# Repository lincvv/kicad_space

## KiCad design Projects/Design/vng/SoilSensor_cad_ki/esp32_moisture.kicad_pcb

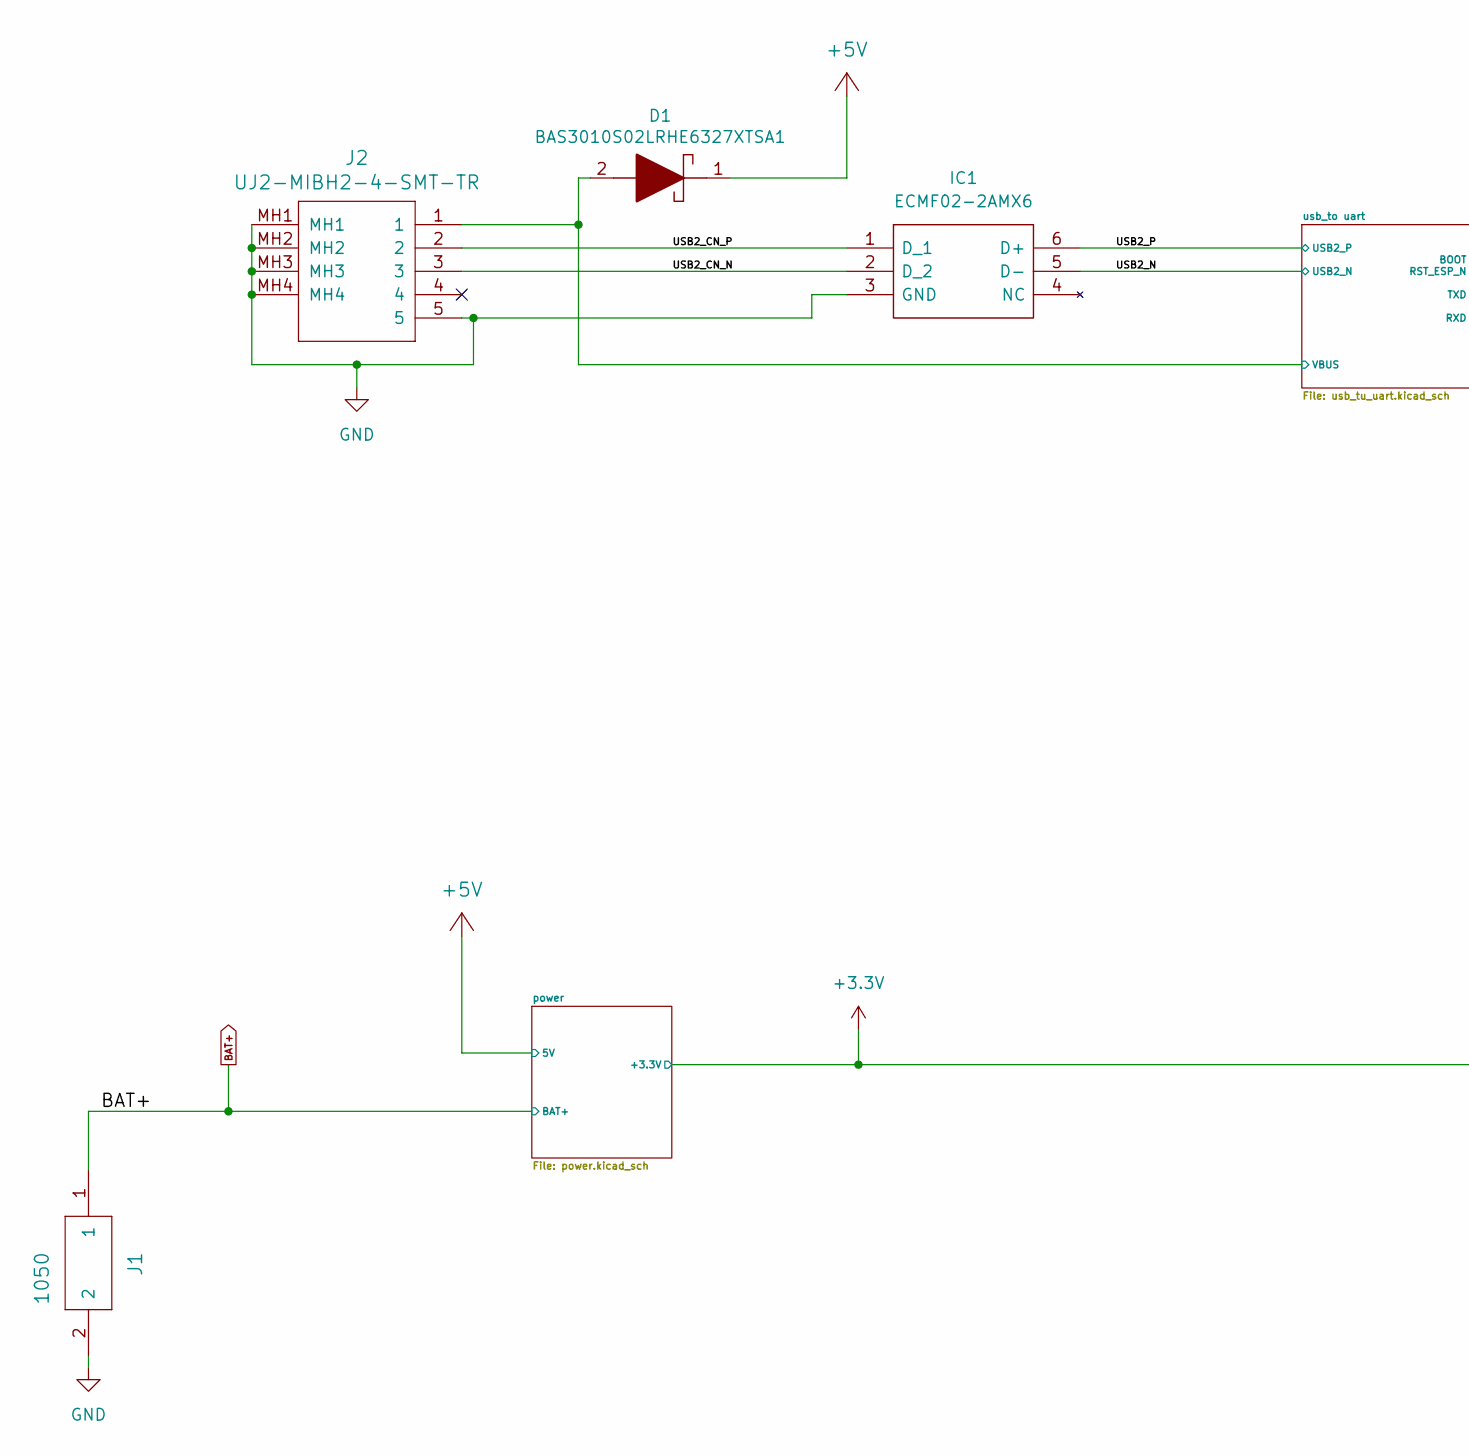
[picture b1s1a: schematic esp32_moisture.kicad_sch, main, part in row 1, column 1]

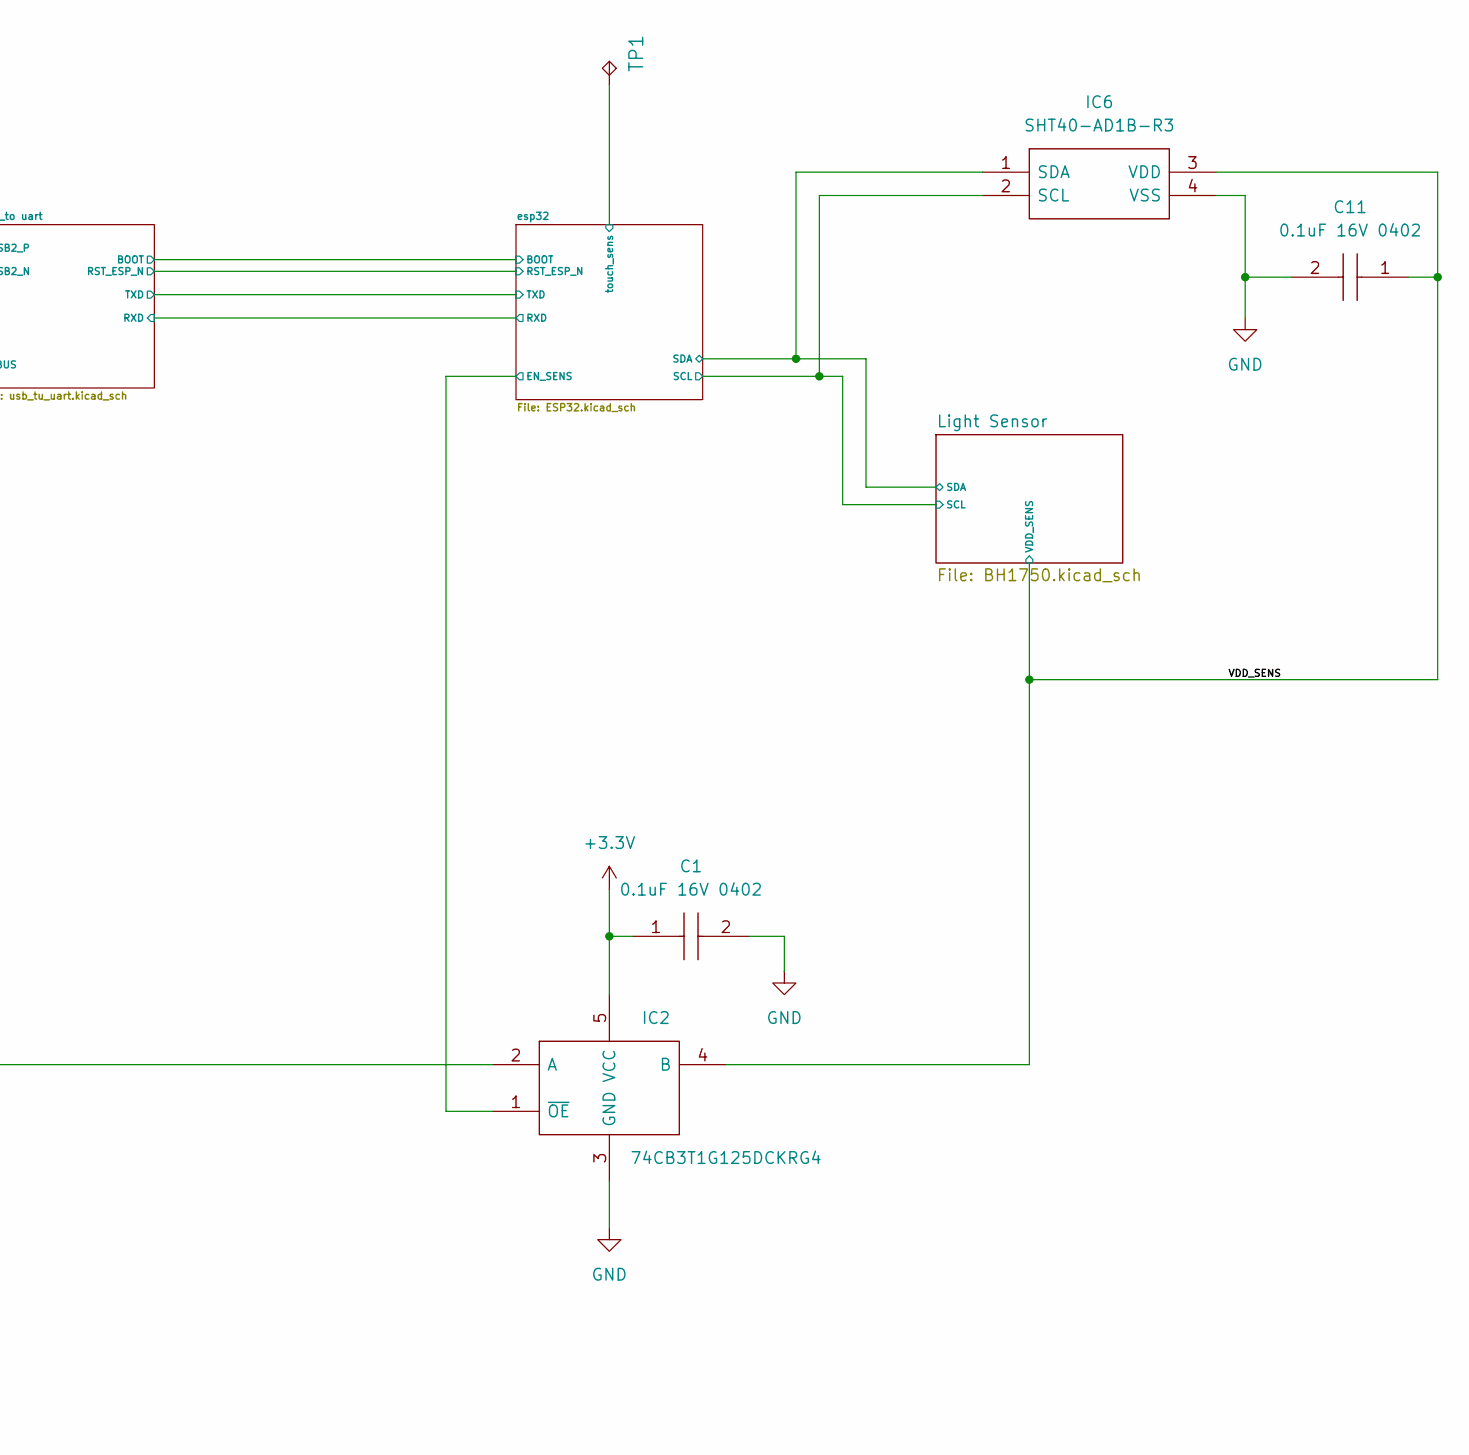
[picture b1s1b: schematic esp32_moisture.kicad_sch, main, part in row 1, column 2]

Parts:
C1, C11: 0.1uF 16V 0402; C_0402_1005Metric; Manufacturer_Part_Number GRM155R71C104KA88D; Mouser Part Number N/A
D1: BAS3010S02LRHE6327XTSA1; Manufacturer_Part_Number BAS3010S02LRHE6327XTSA1; Mouser Part Number 726-3010S02LRHXTSA1
IC1: ECMF02-2AMX6; SON50P150X170X55-6N-D; Manufacturer_Part_Number ECMF02-2AMX6; Mouser Part Number 511-ECMF02-2AMX6
IC2: 74CB3T1G125DCKRG4; SOT65P210X110-5N; Manufacturer_Part_Number 74CB3T1G125DCKRG4; Mouser Part Number 595-CB3T1G125DCKRG4
IC6: SHT40-AD1B-R3; SHT40AD1BR3; Manufacturer_Part_Number SHT40-AD1B-R3; Mouser Part Number 403-SHT40-AD1B-R3
J1: 1050
J2: UJ2-MIBH2-4-SMT-TR; UJ2MIBH24SMTTR
TP1: TPTP15R; TP15R

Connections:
+3.3V: C1.1, IC2.2 (A), IC2.5 (VCC); also elsewhere on the board
+5V: D1.1; also elsewhere on the board
/USB2_CN_N: IC1.2 (D_2), J2.3
/USB2_CN_P: IC1.1 (D_1), J2.2
/USB2_N: IC1.5 (D-); also elsewhere on the board
/USB2_P: IC1.6 (D+); also elsewhere on the board
/VDD_SENS: C11.1, IC2.4 (B), IC6.3 (VDD); also elsewhere on the board
/esp32/EN_SENS: IC2.1 (~OE); also elsewhere on the board
/esp32/SCL: IC6.2 (SCL); also elsewhere on the board
/esp32/SDA: IC6.1 (SDA); also elsewhere on the board
/esp32/touch_sens: TP1.TP; also elsewhere on the board
/usb_to uart/VBUS: D1.2, J2.1; also elsewhere on the board
BAT+: J1.1; also elsewhere on the board
GND: C1.2, C11.2, IC1.3 (GND), IC2.3 (GND), IC6.4 (VSS), J1.2, J2.5, J2.MH1, J2.MH2, J2.MH3, J2.MH4; also elsewhere on the board

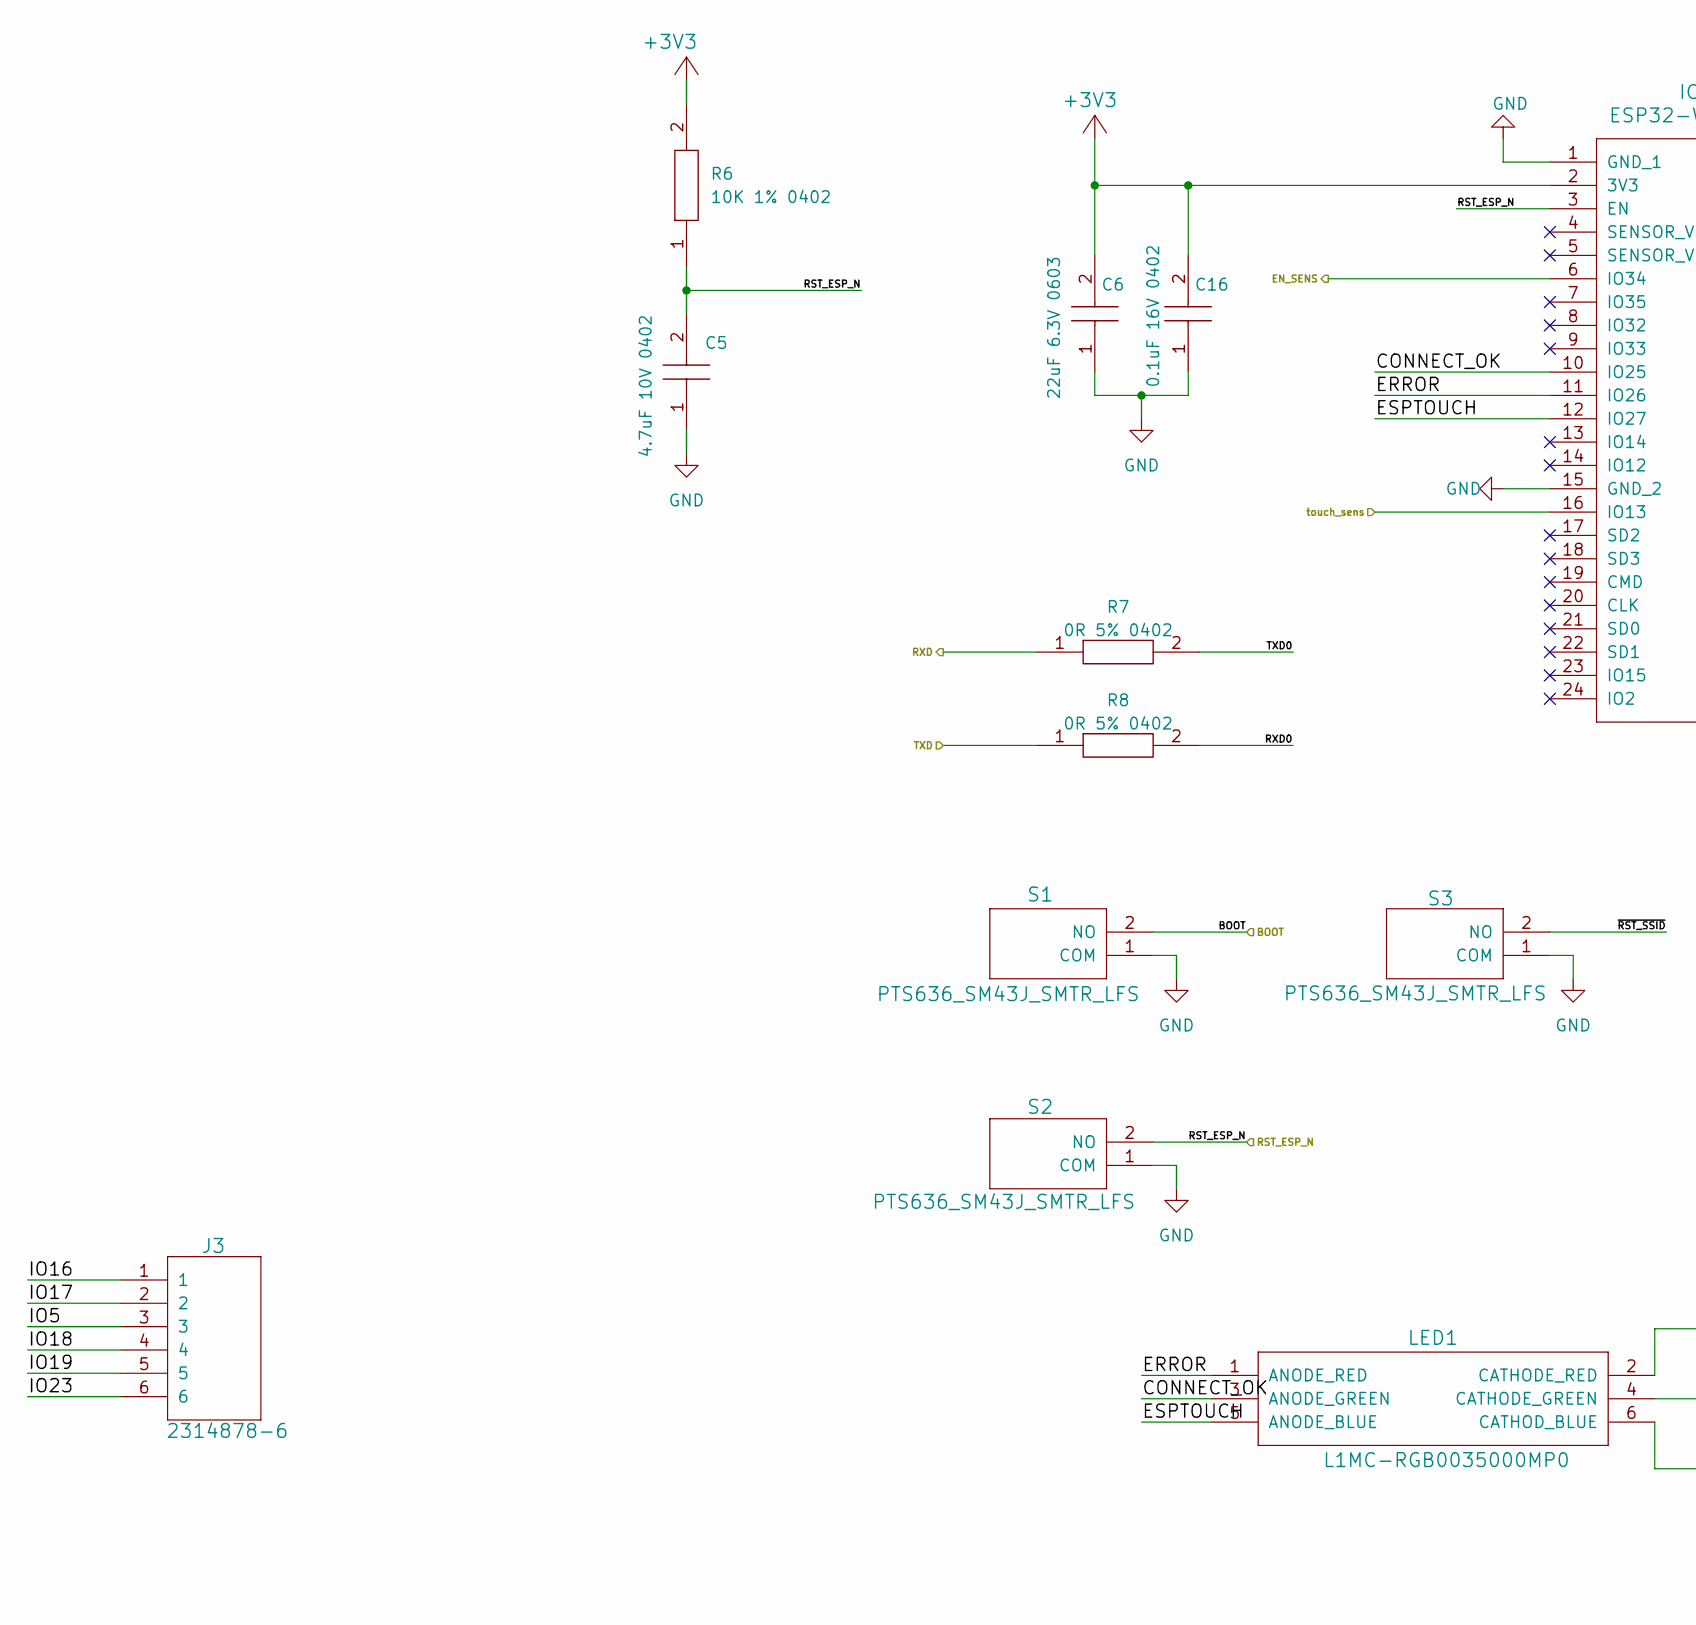
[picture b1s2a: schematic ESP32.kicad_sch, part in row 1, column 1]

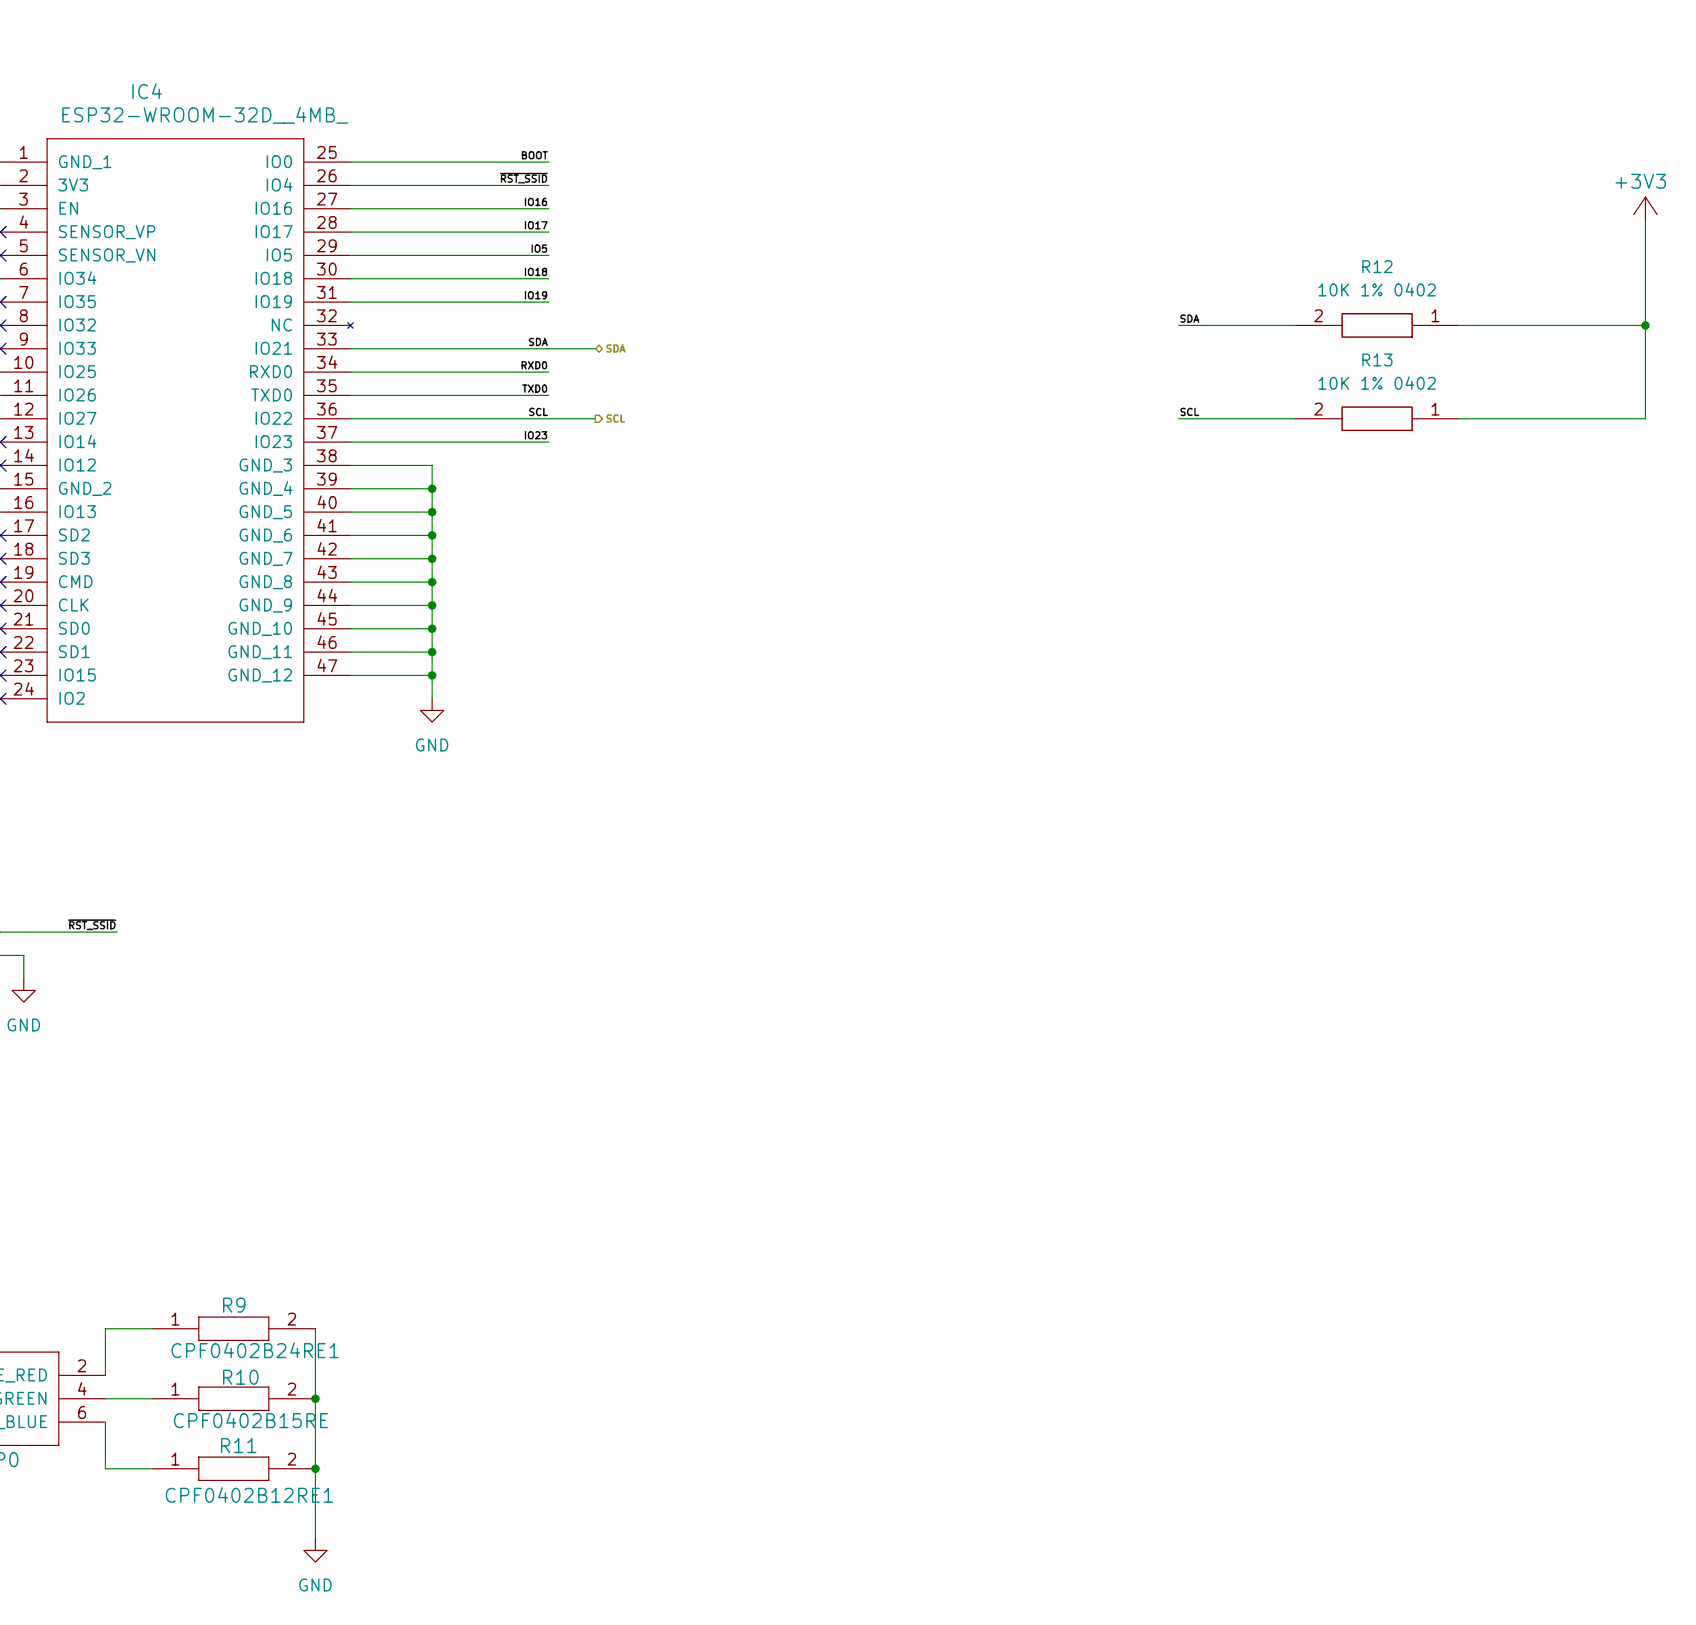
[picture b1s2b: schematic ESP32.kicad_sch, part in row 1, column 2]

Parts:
C5: 4.7uF 10V 0402; C_0402_1005Metric; Manufacturer_Part_Number C1005X5R1A475K050BC; Mouser Part Number 810-C1005X5R1A475KBC
C6: 22uF 6.3V 0603; C_0603_1608Metric; Manufacturer_Part_Number GRM188R60J226MEA0D; Mouser Part Number 81-GRM188R60J226ME0D
C16: 0.1uF 16V 0402; C_0402_1005Metric; Manufacturer_Part_Number GRM155R71C104KA88D; Mouser Part Number N/A
IC4: ESP32-WROOM-32D__4MB_; ESP32WROOM32D4MB
J3: 2314878-6; RHDR6W40P0X200_1X6_1200X210X45
LED1: L1MC-RGB0035000MP0; L1MCRGB0035000MP0
R6, R12, R13: 10K 1% 0402; R_0402_1005Metric; Manufacturer_Part_Number AC0402FR-0710KL; Mouser Part Number 603-AC0402FR-0710KL
R7, R8: 0R 5% 0402; R_0402_1005Metric; Manufacturer_Part_Number CR0402-J/-000GLF; Mouser Part Number 652-CR0402-J/-000GLF
R9: CPF0402B24RE1; RESC1005X35N
R10: CPF0402B15RE; RESC1005X35N
R11: CPF0402B12RE1; RESC1005X35N
S1, S2, S3: PTS636_SM43J_SMTR_LFS; PTS636SM43JSMTRLFS

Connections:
+3V3: C6.2, C16.2, IC4.2 (3V3), R6.2, R12.1, R13.1
/esp32/BOOT: IC4.25 (IO0), S1.2 (NO); also elsewhere on the board
/esp32/CONNECT_OK: IC4.10 (IO25), LED1.3 (ANODE_GREEN)
/esp32/EN_SENS: IC4.6 (IO34); also elsewhere on the board
/esp32/ERROR: IC4.11 (IO26), LED1.1 (ANODE_RED)
/esp32/ESPTOUCH: IC4.12 (IO27), LED1.5 (ANODE_BLUE)
/esp32/IO5: IC4.29 (IO5), J3.3
/esp32/IO16: IC4.27 (IO16), J3.1
/esp32/IO17: IC4.28 (IO17), J3.2
/esp32/IO18: IC4.30 (IO18), J3.4
/esp32/IO19: IC4.31 (IO19), J3.5
/esp32/IO23: IC4.37 (IO23), J3.6
/esp32/RST_ESP_N: C5.2, IC4.3 (EN), R6.1, S2.2 (NO); also elsewhere on the board
/esp32/RXD: R7.1; also elsewhere on the board
/esp32/RXD0: IC4.34 (RXD0), R8.2
/esp32/SCL: IC4.36 (IO22), R13.2; also elsewhere on the board
/esp32/SDA: IC4.33 (IO21), R12.2; also elsewhere on the board
/esp32/TXD: R8.1; also elsewhere on the board
/esp32/TXD0: IC4.35 (TXD0), R7.2
/esp32/touch_sens: IC4.16 (IO13); also elsewhere on the board
/esp32/~RST_SSID: IC4.26 (IO4), S3.2 (NO)
GND: C5.1, C6.1, C16.1, IC4.1 (GND_1), IC4.15 (GND_2), IC4.38 (GND_3), IC4.39 (GND_4), IC4.40 (GND_5), IC4.41 (GND_6), IC4.42 (GND_7), IC4.43 (GND_8), IC4.44 (GND_9), IC4.45 (GND_10), IC4.46 (GND_11), IC4.47 (GND_12), R9.2, R10.2, R11.2, S1.1 (COM), S2.1 (COM), S3.1 (COM); also elsewhere on the board
unnamed: LED1.2 (CATHODE_RED), R9.1
unnamed: LED1.4 (CATHODE_GREEN), R10.1
unnamed: LED1.6 (CATHOD_BLUE), R11.1

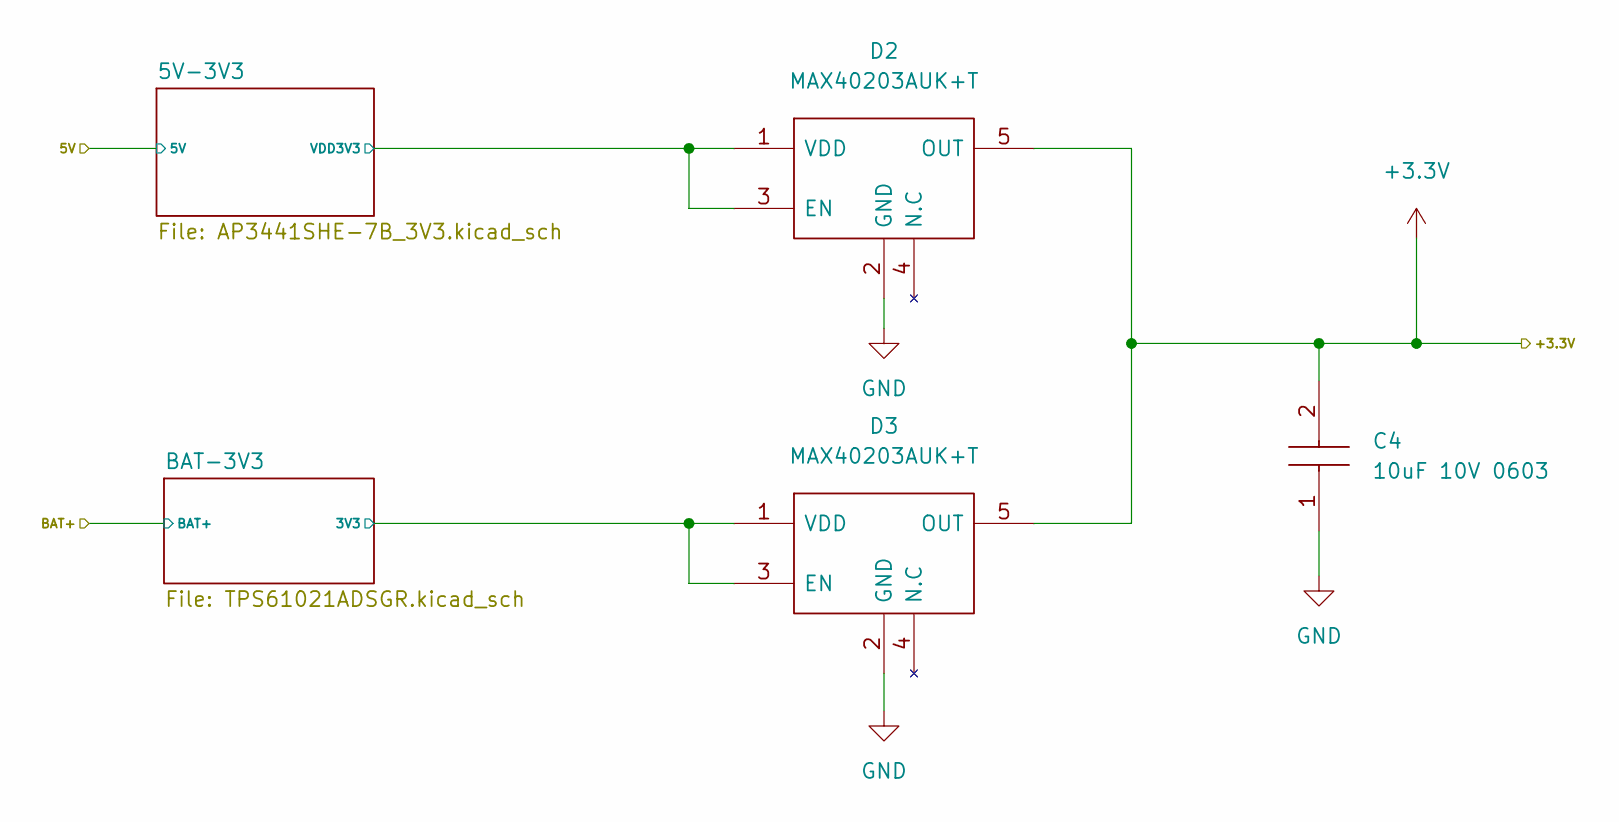
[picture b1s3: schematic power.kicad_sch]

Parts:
C4: 10uF 10V 0603; C_0603_1608Metric; Manufacturer_Part_Number GRM188Z71A106KA73D; Mouser Part Number 81-GRM188Z71A106KA3D
D2, D3: MAX40203AUK+T; SOT95P280X145-5N; Manufacturer_Part_Number MAX40203AUK+T; Mouser Part Number 700-MAX40203AUK+T

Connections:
+3.3V: C4.2, D2.5 (OUT), D3.5 (OUT); also elsewhere on the board
/power/5V-3V3/VDD3V3: D2.1 (VDD), D2.3 (EN); also elsewhere on the board
/power/BAT-3V3/VOUT_3V3: D3.1 (VDD), D3.3 (EN); also elsewhere on the board
GND: C4.1, D2.2 (GND), D3.2 (GND); also elsewhere on the board

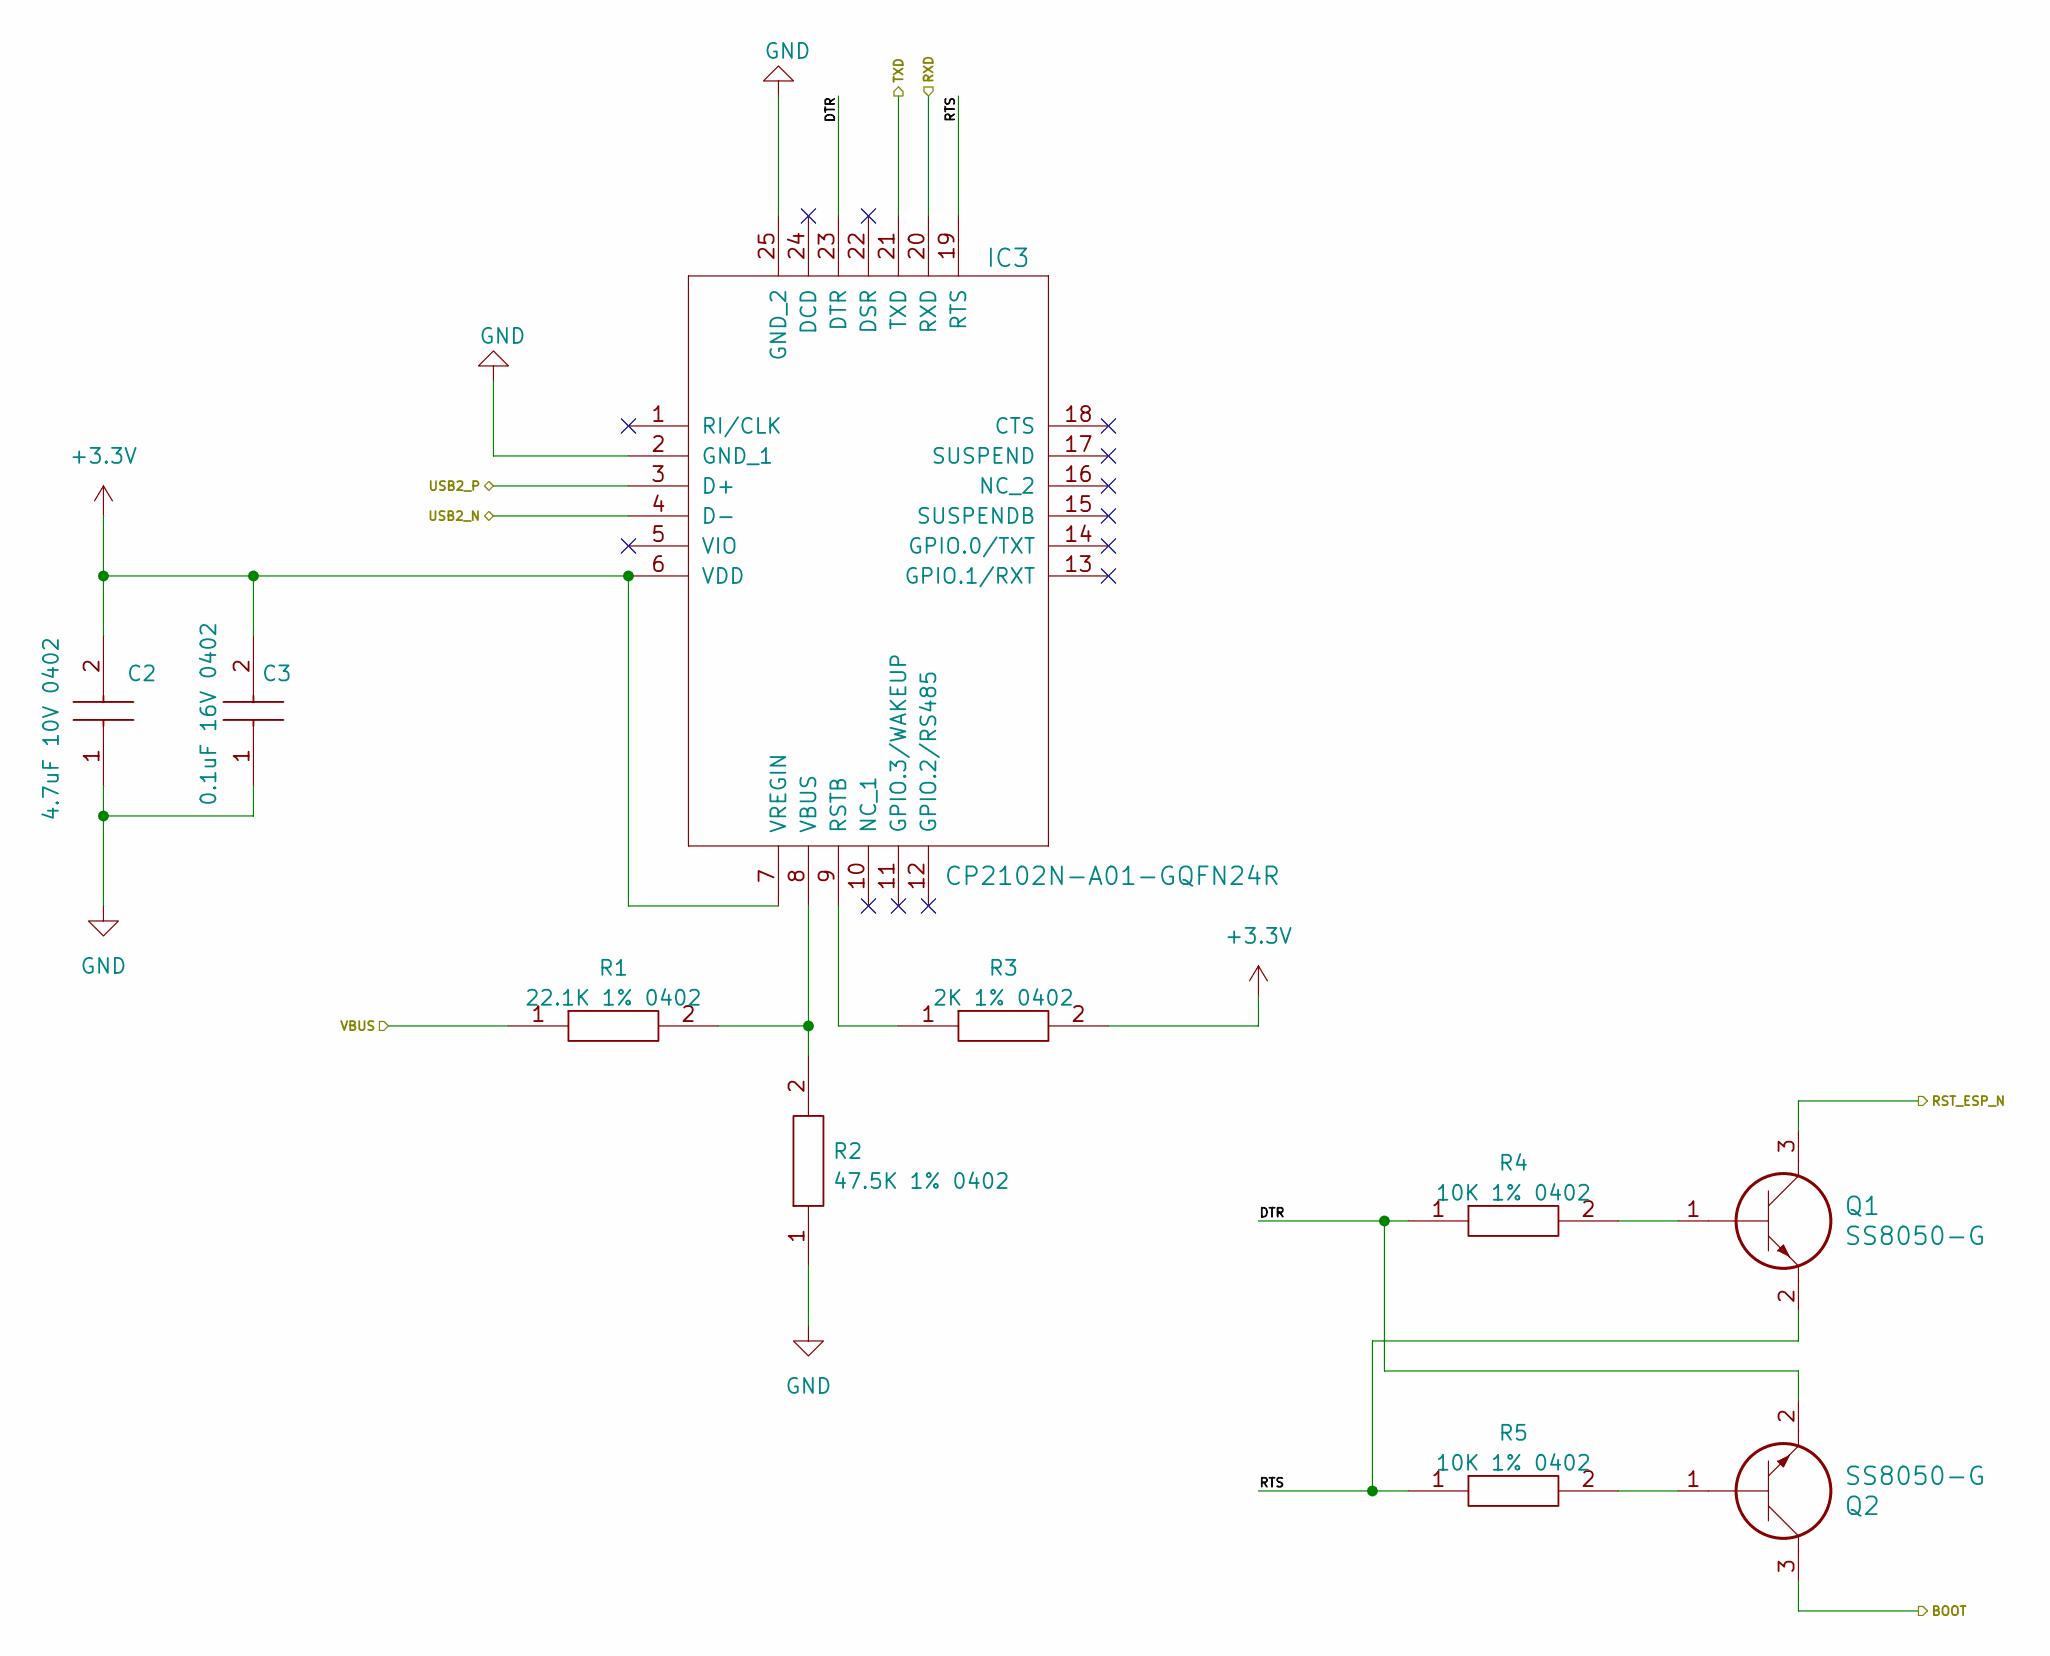
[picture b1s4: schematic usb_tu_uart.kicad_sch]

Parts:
C2: 4.7uF 10V 0402; C_0402_1005Metric; Manufacturer_Part_Number C1005X5R1A475K050BC; Mouser Part Number 810-C1005X5R1A475KBC
C3: 0.1uF 16V 0402; C_0402_1005Metric; Manufacturer_Part_Number GRM155R71C104KA88D; Mouser Part Number N/A
IC3: CP2102N-A01-GQFN24R; QFN50P400X400X80-25N
Q1, Q2: SS8050-G; SOT95P240X115-3N
R1: 22.1K 1% 0402; R_0402_1005Metric; Manufacturer_Part_Number CRCW040222K1FKED; Mouser Part Number 71-CRCW0402-22.1K-E3
R2: 47.5K 1% 0402; R_0402_1005Metric; Manufacturer_Part_Number RC0402FR-0747K5L; Mouser Part Number 603-RC0402FR-0747K5L
R3: 2K 1% 0402; R_0402_1005Metric; Manufacturer_Part_Number CR0402-FX-2001GLF; Mouser Part Number 652-CR0402FX-2001GLF
R4, R5: 10K 1% 0402; R_0402_1005Metric; Manufacturer_Part_Number AC0402FR-0710KL; Mouser Part Number 603-AC0402FR-0710KL

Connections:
+3.3V: C2.2, C3.2, IC3.6 (VDD), IC3.7 (VREGIN), R3.2; also elsewhere on the board
/USB2_N: IC3.4 (D-); also elsewhere on the board
/USB2_P: IC3.3 (D+); also elsewhere on the board
/esp32/BOOT: Q2.3 (C); also elsewhere on the board
/esp32/RST_ESP_N: Q1.3 (C); also elsewhere on the board
/esp32/RXD: IC3.20 (RXD); also elsewhere on the board
/esp32/TXD: IC3.21 (TXD); also elsewhere on the board
/usb_to uart/DTR: IC3.23 (DTR), Q2.2 (E), R4.1
/usb_to uart/RTS: IC3.19 (RTS), Q1.2 (E), R5.1
/usb_to uart/VBUS: R1.1; also elsewhere on the board
GND: C2.1, C3.1, IC3.2 (GND_1), IC3.25 (GND_2), R2.1; also elsewhere on the board
unnamed: IC3.8 (VBUS), R1.2, R2.2
unnamed: IC3.9 (RSTB), R3.1
unnamed: Q1.1 (B), R4.2
unnamed: Q2.1 (B), R5.2

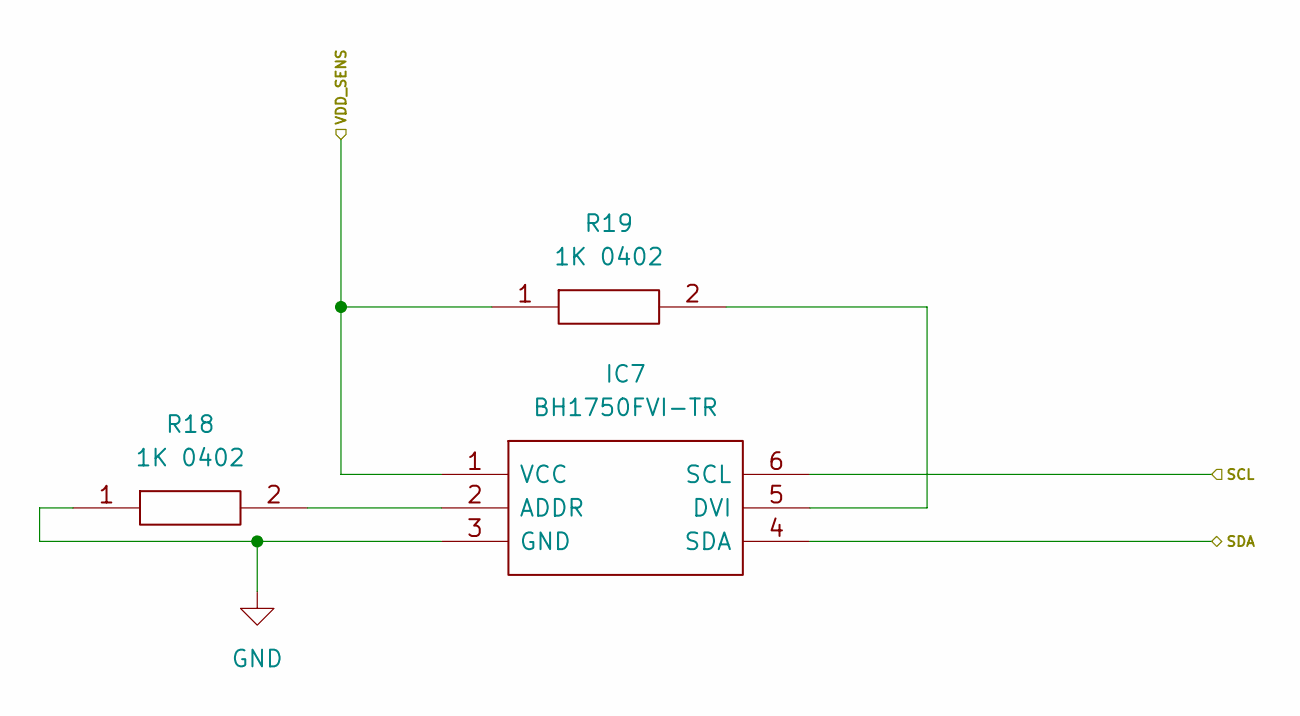
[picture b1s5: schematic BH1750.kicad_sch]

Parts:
IC7: BH1750FVI-TR; WSOF6; Manufacturer_Part_Number BH1750FVI-TR; Mouser Part Number 755-BH1750FVI-TR
R18, R19: 1K 0402; R_0402_1005Metric; Manufacturer_Part_Number RT0402FRE071KL; Mouser Part Number 603-RT0402FRE071KL

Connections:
/VDD_SENS: IC7.1 (VCC), R19.1; also elsewhere on the board
/esp32/SCL: IC7.6 (SCL); also elsewhere on the board
/esp32/SDA: IC7.4 (SDA); also elsewhere on the board
GND: IC7.3 (GND), R18.1; also elsewhere on the board
unnamed: IC7.2 (ADDR), R18.2
unnamed: IC7.5 (DVI), R19.2

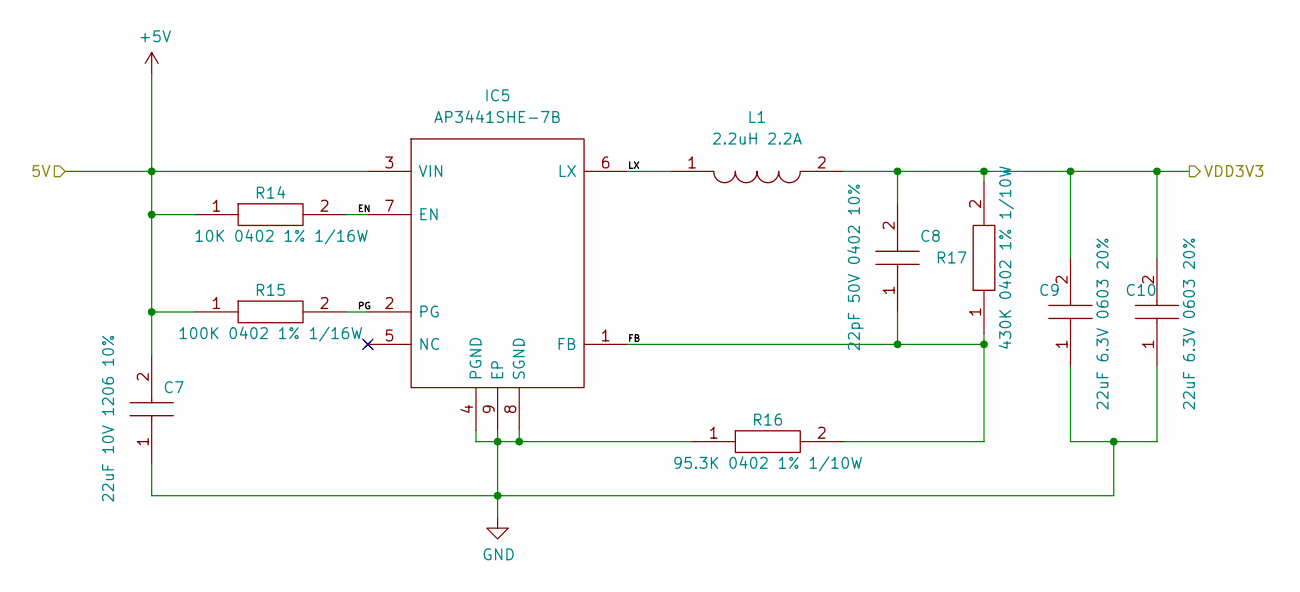
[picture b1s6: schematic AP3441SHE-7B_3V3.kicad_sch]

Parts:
C7: 22uF 10V 1206 10%; C_1206_3216Metric; Manufacturer_Part_Number GRM31CR71A226KE15L; Mouser Part Number 81-GRM31CR71A226K15L
C8: 22pF 50V 0402 10%; C_0402_1005Metric; Manufacturer_Part_Number C0402C220K5RACTU; Mouser Part Number 80-C0402C220K5RACTU
C9, C10: 22uF 6.3V 0603 20%; C_0603_1608Metric; Manufacturer_Part_Number GRM188R60J226MEA0D; Mouser Part Number 81-GRM188R60J226ME0D
IC5: AP3441SHE-7B; SON50P201X201X60-9N-D; Manufacturer_Part_Number AP3441SHE-7B; Mouser Part Number 621-AP3441SHE-7B
L1: 2.2uH 2.2A; DFE2HCAH1R0MJ0L; Manufacturer_Part_Number 1239AS-H-2R2M=P2; Mouser Part Number 81-1239AS-H-2R2MP2
R14: 10K 0402 1% 1/16W; R_0402_1005Metric; Manufacturer_Part_Number AC0402FR-0710KL; Mouser Part Number 603-AC0402FR-0710KL
R15: 100K 0402 1% 1/16W; R_0402_1005Metric; Manufacturer_Part_Number SFR01MZPF1003; Mouser Part Number 755-SFR01MZPF1003
R16: 95.3K 0402 1% 1/10W; R_0402_1005Metric; Manufacturer_Part_Number ERJ-U02F9532X; Mouser Part Number 667-ERJ-U02F9532X
R17: 430K 0402 1% 1/10W; R_0402_1005Metric; Manufacturer_Part_Number ERJ-U02F4303X

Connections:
+5V: C7.2, IC5.3 (VIN), R14.1, R15.1; also elsewhere on the board
/power/5V-3V3/EN: IC5.7 (EN), R14.2
/power/5V-3V3/FB: C8.1, IC5.1 (FB), R16.2, R17.1
/power/5V-3V3/LX: IC5.6 (LX), L1.1
/power/5V-3V3/PG: IC5.2 (PG), R15.2
/power/5V-3V3/VDD3V3: C8.2, C9.2, C10.2, L1.2, R17.2; also elsewhere on the board
GND: C7.1, C9.1, C10.1, IC5.4 (PGND), IC5.8 (SGND), IC5.9 (EP), R16.1; also elsewhere on the board

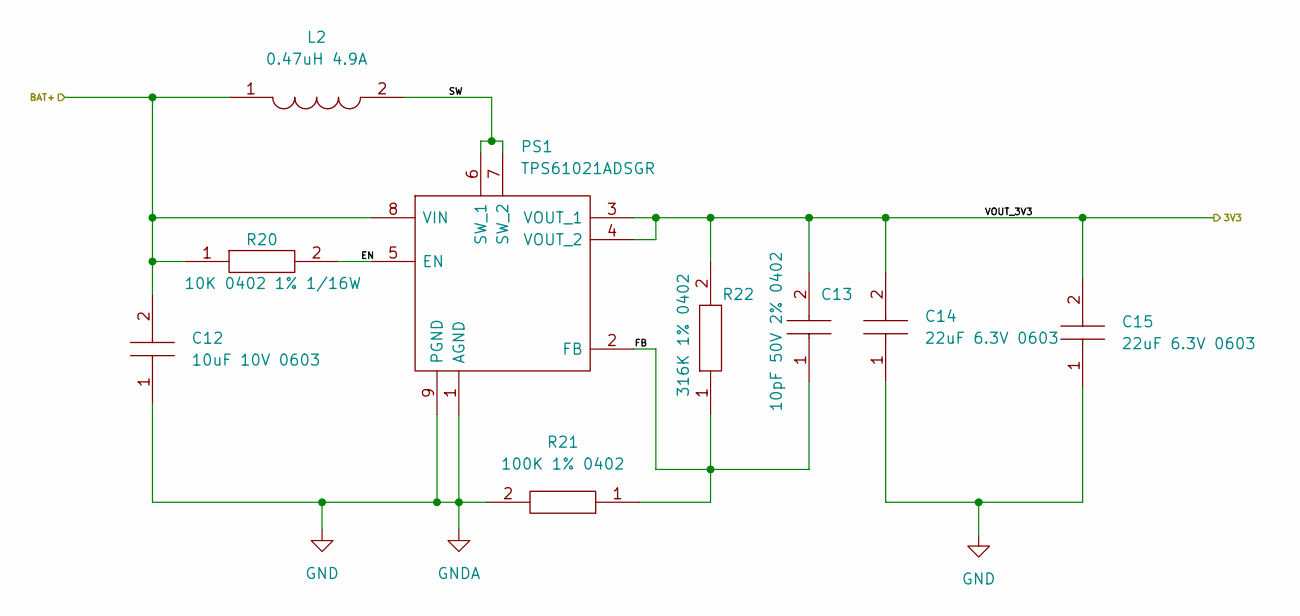
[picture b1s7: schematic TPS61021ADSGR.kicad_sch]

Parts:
C12: 10uF 10V 0603; C_0603_1608Metric; Manufacturer_Part_Number GRM188Z71A106KA73D; Mouser Part Number 81-GRM188Z71A106KA3D
C13: 10pF 50V 2% 0402; C_0402_1005Metric; Manufacturer_Part_Number GJM1555C1H100GB01D; Mouser Part Number 81-GJM1555C1H100GB01
C14, C15: 22uF 6.3V 0603; C_0603_1608Metric; Manufacturer_Part_Number GRM188R60J226MEA0D; Mouser Part Number 81-GRM188R60J226ME0D
L2: 0.47uH 4.9A; INDC2016X80N; Manufacturer_Part_Number TFM201610ALC-R47MTAA; Mouser Part Number 810-TFM201610ALCR47M
PS1: TPS61021ADSGR; SON50P200X200X80-9N; Manufacturer_Part_Number TPS61021ADSGR; Mouser Part Number 595-TPS61021ADSGR
R20: 10K 0402 1% 1/16W; R_0402_1005Metric; Manufacturer_Part_Number AC0402FR-0710KL; Mouser Part Number 603-AC0402FR-0710KL
R21: 100K 1% 0402; R_0402_1005Metric; Manufacturer_Part_Number SFR01MZPF1003; Mouser Part Number 755-SFR01MZPF1003
R22: 316K 1% 0402; R_0402_1005Metric; Manufacturer_Part_Number CR0402-FX-3163GLF; Mouser Part Number 652-CR0402FX3163GLF

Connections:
/power/BAT-3V3/EN: PS1.5 (EN), R20.2
/power/BAT-3V3/FB: C13.1, PS1.2 (FB), R21.1, R22.1
/power/BAT-3V3/SW: L2.2, PS1.6 (SW_1), PS1.7 (SW_2)
/power/BAT-3V3/VOUT_3V3: C13.2, C14.2, C15.2, PS1.3 (VOUT_1), PS1.4 (VOUT_2), R22.2; also elsewhere on the board
BAT+: C12.2, L2.1, PS1.8 (VIN), R20.1; also elsewhere on the board
GND: C12.1, C14.1, C15.1, PS1.1 (AGND), PS1.9 (PGND), R21.2; also elsewhere on the board

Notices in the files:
parts and their libraries:
Copyright 2021 Accelerated Designs. All rights reserved.
